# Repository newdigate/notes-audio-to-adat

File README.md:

# notes-audio-to-adat
* scrapbook for notes for audio-to-opto

# chipsets
## cool-audio
* http://coolaudio.com/docs/COOLAUDIO_V1401_DATASHEET.pdf
* http://coolaudio.com/docs/COOLAUDIO_V1402_DATASHEET.pdf

## wavefront 
* AL1401A
 * [datasheet](http://pdf.datasheetcatalog.com/datasheets2/15/156040_1.pdf)

# ADC
* Cirrus Logic 
  * CS5368-CQZ [datasheet](http://datasheet.octopart.com/CS5368-CQZ-Cirrus-Logic-datasheet-13402503.pdf)

# optical connectors
* TORX147 optical receiver
* PLR135/T10
  * PLR135 Series 2.4 to 5.5 V 16 Mbps 650 nm Photolink Fiber Optic Receiver
    * [snapEDA](https://www.snapeda.com/parts/PLR135/T10/Everlight%20Electronics%20Co%20Ltd/view-part/?ref=search&t=PLR135)
* Toshiba TOTX173
  * [octopart](https://octopart.com/totx173-toshiba-2173863?r=sp&s=UF4sqbTzTXCrdWtcyLfNBw)
  
# logic level converters
* AL1401A uses 5V logic, 3v3 to 5v required
* Texas Instruments 
  * CD40109BNSRG4 [datasheet](https://octopart.com/click/track?ct=datasheets&hlid=24875070&ppid=7109542&sid=370&sig=0583e53)
* The output signal of the AL1401 (i.e. to the fibre-optic LED) is ~0.9V, which needs to be converted to  between 2.5V and 5V5.

# micro-controllers
* xmos
  * XE216-512-TQ128-C20 (	digikey £12.43)

# reference designs
* https://www.xmos.com/download/xCORE-200-Multichannel-Audio-Platform-2V0-Hardware-Manual(1.4).pdf/

# misc links
https://jirin.web.althan.cz/201404-adater-the-lightpipe-interface-for-delta1010-rack/#

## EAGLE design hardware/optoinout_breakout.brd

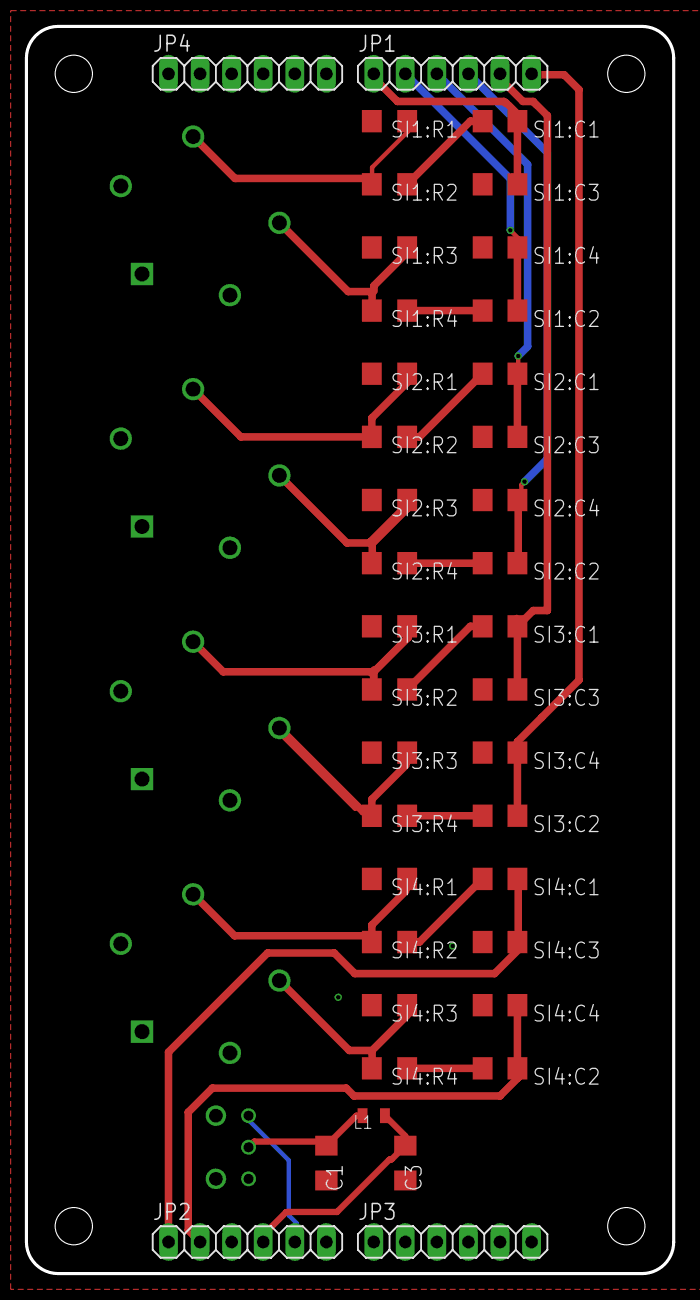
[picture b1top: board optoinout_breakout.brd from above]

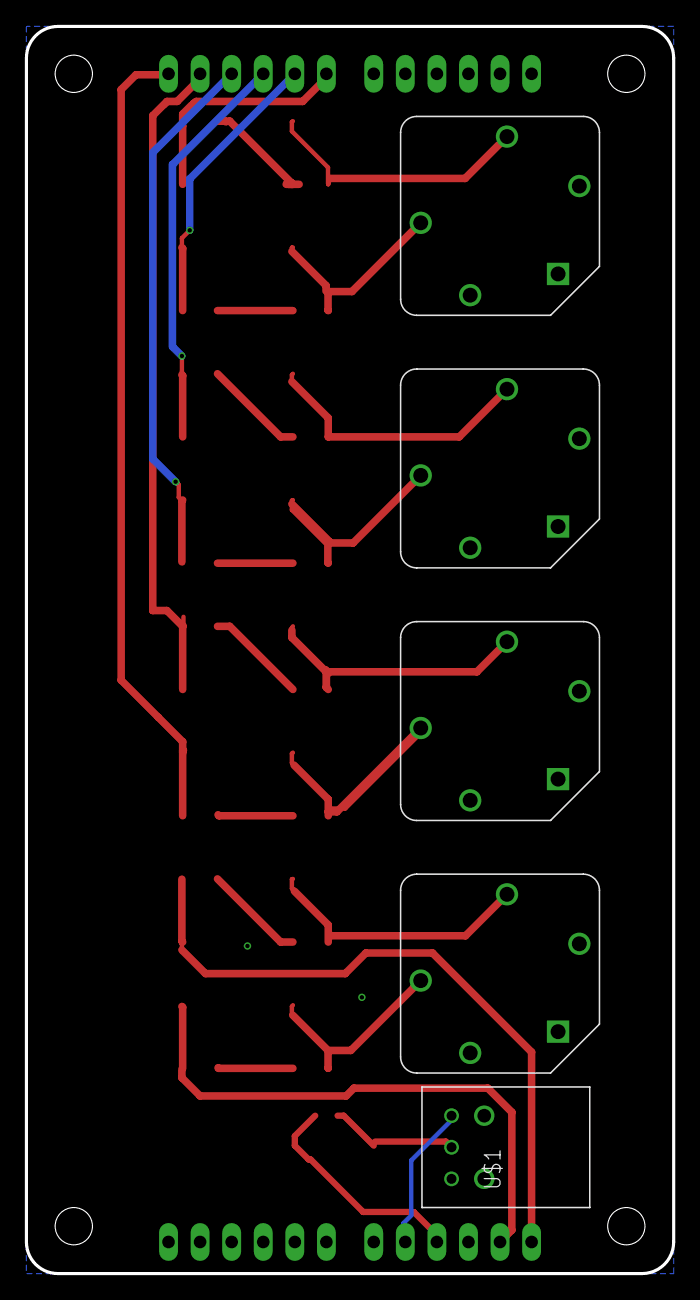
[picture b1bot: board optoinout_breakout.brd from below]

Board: 2 copper layers, 52.1 x 100.3 mm, 44 parts (5 on the bottom side), 28 nets.

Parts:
C1, C3: 100nF; C1206
JP1, JP2, JP3, JP4: 1X06
L1: 470R 500mA; L0805
SI1:C1, SI1:C2, SI2:C1, SI2:C2, SI3:C1, SI3:C2, SI4:C1, SI4:C2: 10uF; C1206
SI1:C3, SI1:C4, SI2:C3, SI2:C4, SI3:C3, SI3:C4, SI4:C3, SI4:C4: 2700pF; C1206
SI1:R1, SI1:R3, SI2:R1, SI2:R3, SI3:R1, SI3:R3, SI4:R1, SI4:R3: 100K; R1206
SI1:R2, SI1:R4, SI2:R2, SI2:R4, SI3:R2, SI3:R4, SI4:R2, SI4:R4: 150; R1206
SI1:U$3, SI2:U$3, SI3:U$3, SI4:U$3: ACJS-MV-5; ACJS-MV5
U$1: PLT133-T10W; PLR135-T10_PLT133-T10W

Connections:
3V3: C3.1, JP2.4, L1.P$1
AIN1+: JP1.1, SI1:C1.1, SI1:C3.1
AIN2+: JP1.2, SI1:C2.1, SI1:C4.1
AIN3+: JP1.3, SI2:C1.1, SI2:C3.1
AIN4+: JP1.4, SI2:C2.1, SI2:C4.1
AIN5+: JP1.5, SI3:C1.1, SI3:C3.1
AIN6+: JP1.6, SI3:C2.1, SI3:C4.1
AIN7+: JP2.1, SI4:C1.1, SI4:C3.1
AIN8+: JP2.2, SI4:C2.1, SI4:C4.1
GND: C1.2, C3.2, JP2.3, SI1:C3.2, SI1:C4.2, SI1:R1.1, SI1:R3.1, SI1:U$3.P$1, SI1:U$3.P$2, SI1:U$3.P$5, SI2:C3.2, SI2:C4.2, SI2:R1.1, SI2:R3.1, SI2:U$3.P$1, SI2:U$3.P$2, SI2:U$3.P$5, SI3:C3.2, SI3:C4.2, SI3:R1.1, SI3:R3.1, SI3:U$3.P$1, SI3:U$3.P$2, SI3:U$3.P$5, SI4:C3.2, SI4:C4.2, SI4:R1.1, SI4:R3.1, SI4:U$3.P$1, SI4:U$3.P$2, SI4:U$3.P$5, U$1.1
unnamed: C1.1, L1.P$2, U$1.2
OPOUT: JP2.5, U$1.3
SI1:N$1: SI1:R1.2, SI1:R2.1, SI1:U$3.P$4
SI1:N$7: SI1:C1.2, SI1:R2.2
SI1:N$10: SI1:R3.2, SI1:R4.1, SI1:U$3.P$3
SI1:N$11: SI1:C2.2, SI1:R4.2
SI2:N$1: SI2:R1.2, SI2:R2.1, SI2:U$3.P$4
SI2:N$7: SI2:C1.2, SI2:R2.2
SI2:N$10: SI2:R3.2, SI2:R4.1, SI2:U$3.P$3
SI2:N$11: SI2:C2.2, SI2:R4.2
SI3:N$1: SI3:R1.2, SI3:R2.1, SI3:U$3.P$4
SI3:N$7: SI3:C1.2, SI3:R2.2
SI3:N$10: SI3:R3.2, SI3:R4.1, SI3:U$3.P$3
SI3:N$11: SI3:C2.2, SI3:R4.2
SI4:N$1: SI4:R1.2, SI4:R2.1, SI4:U$3.P$4
SI4:N$7: SI4:C1.2, SI4:R2.2
SI4:N$10: SI4:R3.2, SI4:R4.1, SI4:U$3.P$3
SI4:N$11: SI4:C2.2, SI4:R4.2

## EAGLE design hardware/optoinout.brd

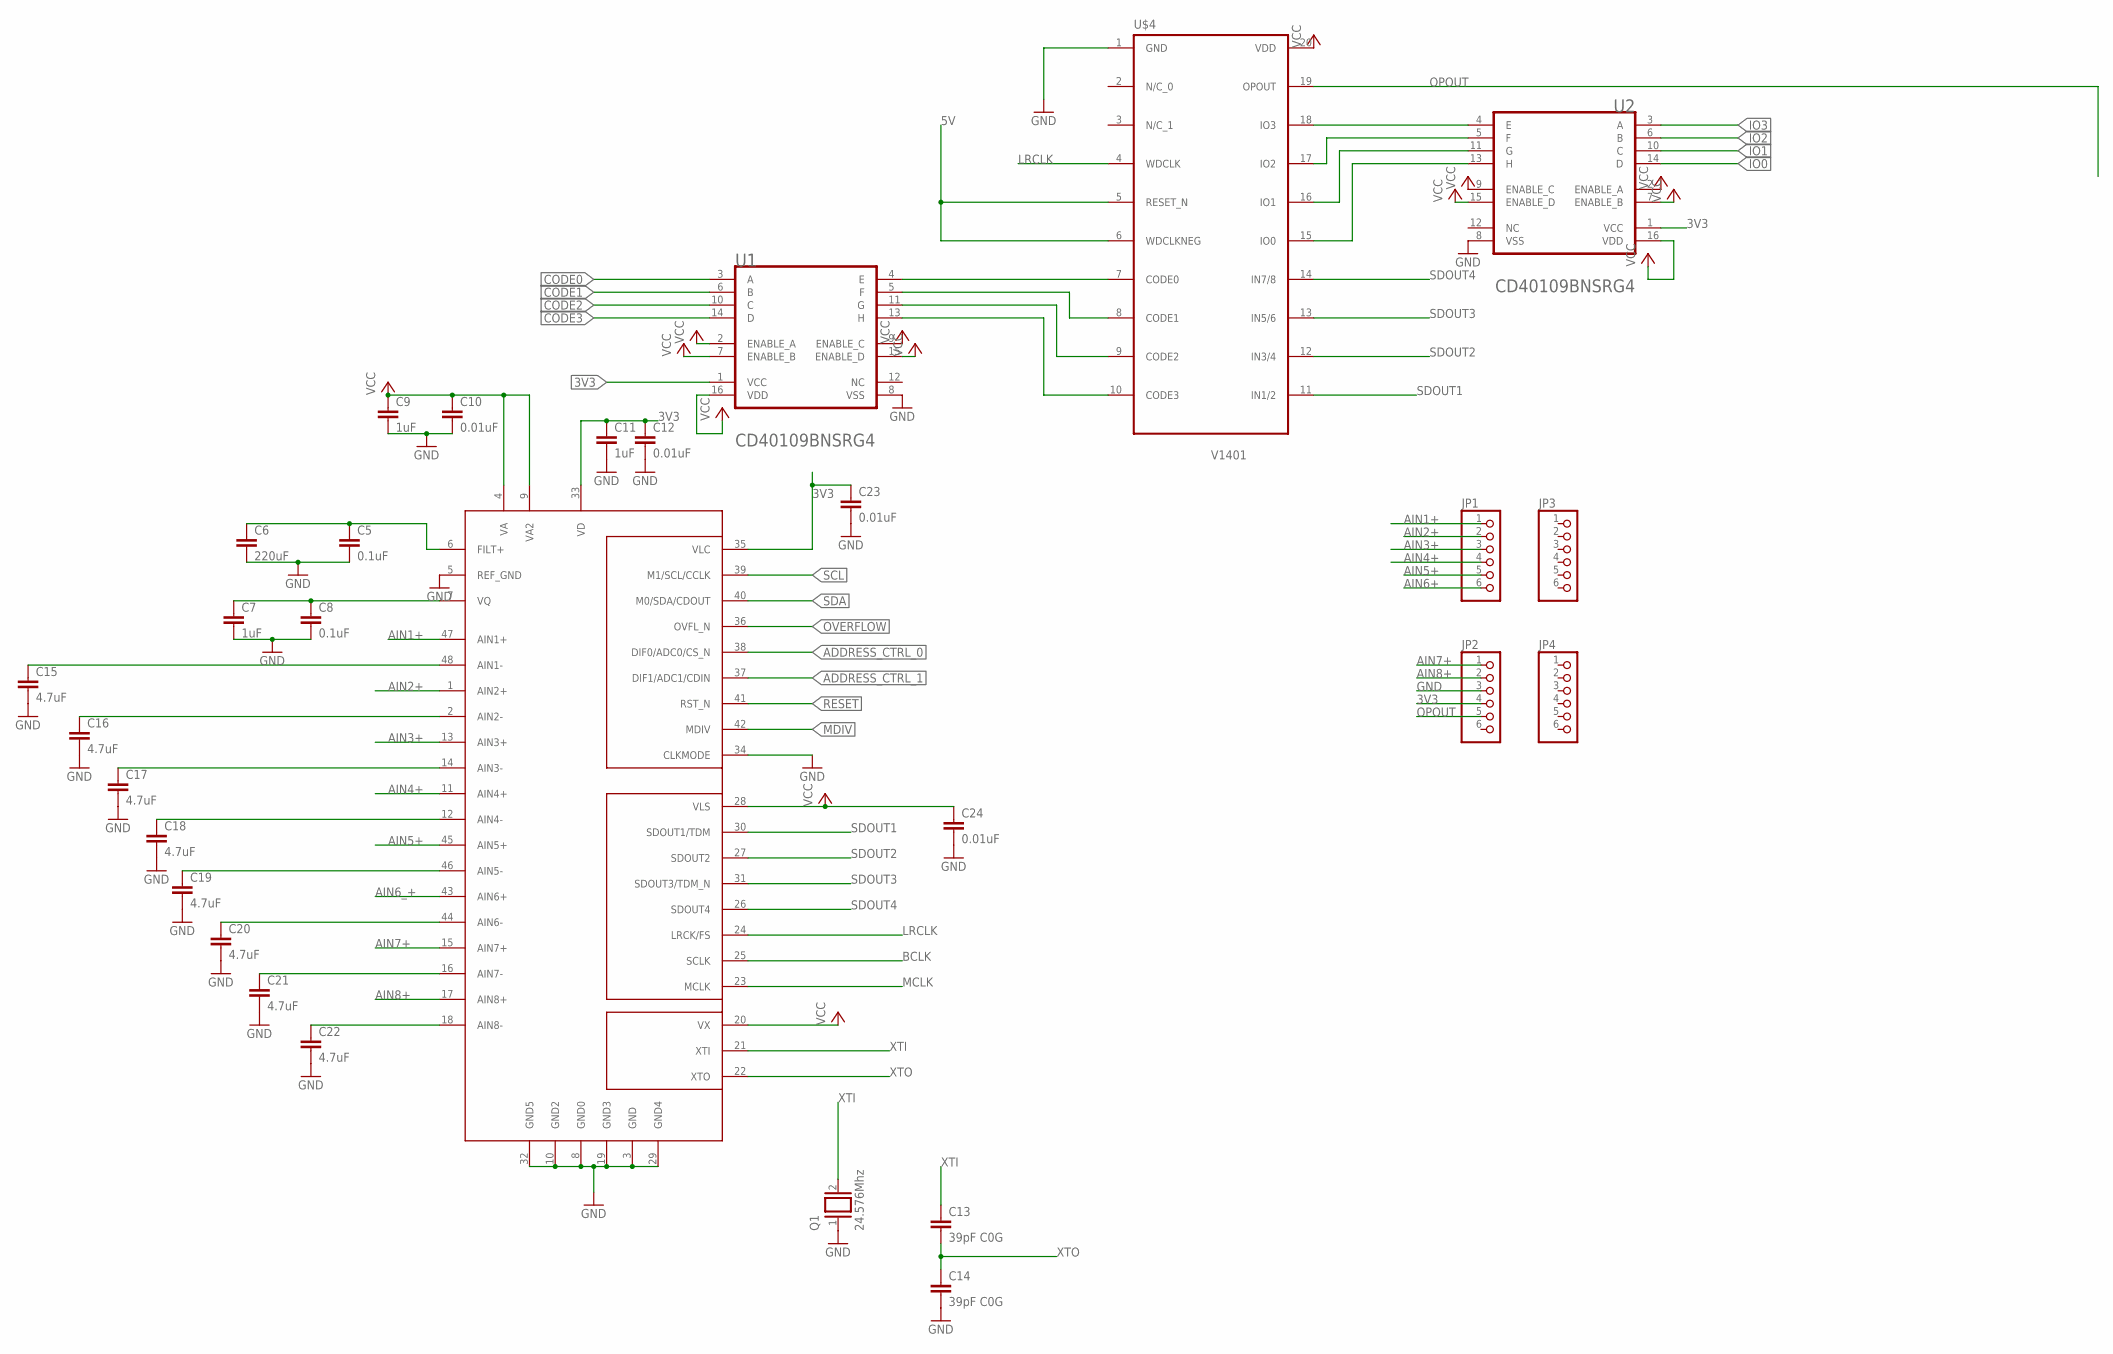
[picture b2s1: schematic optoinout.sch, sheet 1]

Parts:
C5, C8: 0.1uF; C1206
C6: 220uF; C1206
C7, C9, C11: 1uF; C1206
C10, C12, C23, C24: 0.01uF; C1206
C13, C14: 39pF C0G; C1206
C15, C16, C17, C18, C19, C20, C21, C22: 4.7uF; C1206
JP1, JP2, JP3, JP4: PINHD-1X6; 1X06
Q1: 24.576Mhz; QS
U1, U2: TEXAS_INSTRUMENTS_CD40109BNSRG4TEXAS_INSTRUMENTS_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; TEXAS_INSTRUMENTS_CD40109BNSRG4_0
U$3: CS5368-2; QFP50P900X900X160-48N
U$4: V1401; SOP20

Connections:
3V3: C11.1, C12.1, C23.1, JP2.4, U1.1 (VCC), U2.1 (VCC), U$3.33 (VD), U$3.35 (VLC); also elsewhere on the board
5V: U$4.5 (RESET_N), U$4.6 (WDCLKNEG)
ADDRESS_CTRL_0: U$3.38 (DIF0/ADC0/CS_N); also elsewhere on the board
ADDRESS_CTRL_1: U$3.37 (DIF1/ADC1/CDIN); also elsewhere on the board
AIN1+: JP1.1, U$3.47 (AIN1+)
AIN2+: JP1.2, U$3.1 (AIN2+)
AIN3+: JP1.3, U$3.13 (AIN3+)
AIN4+: JP1.4, U$3.11 (AIN4+)
AIN5+: JP1.5, U$3.45 (AIN5+)
AIN6+: JP1.6
AIN6_+: U$3.43 (AIN6+)
AIN7+: JP2.1, U$3.15 (AIN7+)
AIN8+: JP2.2, U$3.17 (AIN8+)
BCLK: U$3.25 (SCLK)
CODE0: U1.3 (A); also elsewhere on the board
CODE1: U1.6 (B); also elsewhere on the board
CODE2: U1.10 (C); also elsewhere on the board
CODE3: U1.14 (D); also elsewhere on the board
GND: C5.2, C6.2, C7.2, C8.2, C9.2, C10.2, C11.2, C12.2, C14.2, C15.2, C16.2, C17.2, C18.2, C19.2, C20.2, C21.2, C22.2, C23.2, C24.2, JP2.3, Q1.1, U1.8 (VSS), U2.8 (VSS), U$3.3 (GND), U$3.5 (REF_GND), U$3.8 (GND0), U$3.10 (GND2), U$3.19 (GND3), U$3.29 (GND4), U$3.32 (GND5), U$3.34 (CLKMODE), U$4.1 (GND); also elsewhere on the board
IO0: U2.14 (D); also elsewhere on the board
IO1: U2.10 (C); also elsewhere on the board
IO2: U2.6 (B); also elsewhere on the board
IO3: U2.3 (A); also elsewhere on the board
LRCLK: U$3.24 (LRCK/FS), U$4.4 (WDCLK)
MCLK: U$3.23 (MCLK)
MDIV: U$3.42 (MDIV); also elsewhere on the board
unnamed: C7.1, C8.1, U$3.7 (VQ)
unnamed: U1.4 (E), U$4.7 (CODE0)
unnamed: C5.1, C6.1, U$3.6 (FILT+)
unnamed: U1.5 (F), U$4.8 (CODE1)
unnamed: U1.11 (G), U$4.9 (CODE2)
unnamed: U1.13 (H), U$4.10 (CODE3)
unnamed: C16.1, U$3.2 (AIN2-)
unnamed: C15.1, U$3.48 (AIN1-)
unnamed: C17.1, U$3.14 (AIN3-)
unnamed: C18.1, U$3.12 (AIN4-)
unnamed: C19.1, U$3.46 (AIN5-)
unnamed: C20.1, U$3.44 (AIN6-)
unnamed: C21.1, U$3.16 (AIN7-)
unnamed: C22.1, U$3.18 (AIN8-)
unnamed: U2.4 (E), U$4.18 (IO3)
unnamed: U2.5 (F), U$4.17 (IO2)
unnamed: U2.11 (G), U$4.16 (IO1)
unnamed: U2.13 (H), U$4.15 (IO0)
OPOUT: JP2.5, U$4.19 (OPOUT)
OVERFLOW: U$3.36 (OVFL_N); also elsewhere on the board
RESET: U$3.41 (RST_N); also elsewhere on the board
SCL: U$3.39 (M1/SCL/CCLK); also elsewhere on the board
SDA: U$3.40 (M0/SDA/CDOUT); also elsewhere on the board
SDOUT1: U$3.30 (SDOUT1/TDM), U$4.11 (IN1/2)
SDOUT2: U$3.27 (SDOUT2), U$4.12 (IN3/4)
SDOUT3: U$3.31 (SDOUT3/TDM_N), U$4.13 (IN5/6)
SDOUT4: U$3.26 (SDOUT4), U$4.14 (IN7/8)
VCC: C9.1, C10.1, C24.1, U1.2 (ENABLE_A), U1.7 (ENABLE_B), U1.9 (ENABLE_C), U1.15 (ENABLE_D), U1.16 (VDD), U2.2 (ENABLE_A), U2.7 (ENABLE_B), U2.9 (ENABLE_C), U2.15 (ENABLE_D), U2.16 (VDD), U$3.4 (VA), U$3.9 (VA2), U$3.20 (VX), U$3.28 (VLS), U$4.20 (VDD); also elsewhere on the board
XTI: C13.1, Q1.2, U$3.21 (XTI)
XTO: C13.2, C14.1, U$3.22 (XTO)

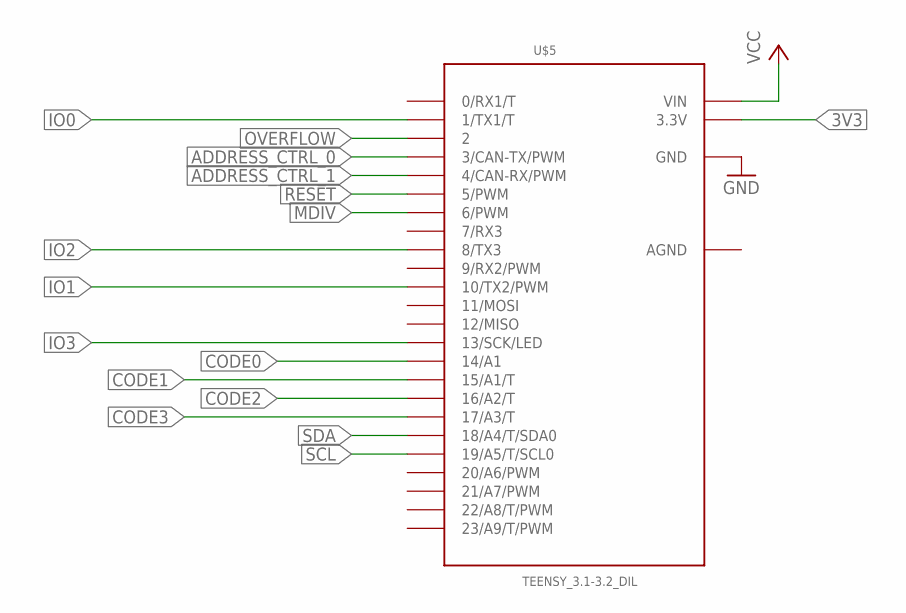
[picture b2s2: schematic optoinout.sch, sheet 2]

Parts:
U$5: TEENSY_3.1-3.2_DIL; TEENSY_3.0-3.2&LC_DIL

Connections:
3V3: U$5.3.3V; also elsewhere on the board
ADDRESS_CTRL_0: U$5.3 (3/CAN-TX/PWM); also elsewhere on the board
ADDRESS_CTRL_1: U$5.4 (4/CAN-RX/PWM); also elsewhere on the board
AGND: U$5.AGND
CODE0: U$5.14/A0 (14/A1); also elsewhere on the board
CODE1: U$5.15/A1 (15/A1/T); also elsewhere on the board
CODE2: U$5.16/A2 (16/A2/T); also elsewhere on the board
CODE3: U$5.17/A3 (17/A3/T); also elsewhere on the board
GND: U$5.GND; also elsewhere on the board
IO0: U$5.1 (1/TX1/T); also elsewhere on the board
IO1: U$5.10 (10/TX2/PWM); also elsewhere on the board
IO2: U$5.8 (8/TX3); also elsewhere on the board
IO3: U$5.13 (13/SCK/LED); also elsewhere on the board
MDIV: U$5.6 (6/PWM); also elsewhere on the board
OVERFLOW: U$5.2; also elsewhere on the board
RESET: U$5.5 (5/PWM); also elsewhere on the board
SCL: U$5.19/A5 (19/A5/T/SCL0); also elsewhere on the board
SDA: U$5.18/A4 (18/A4/T/SDA0); also elsewhere on the board
VCC: U$5.VIN; also elsewhere on the board

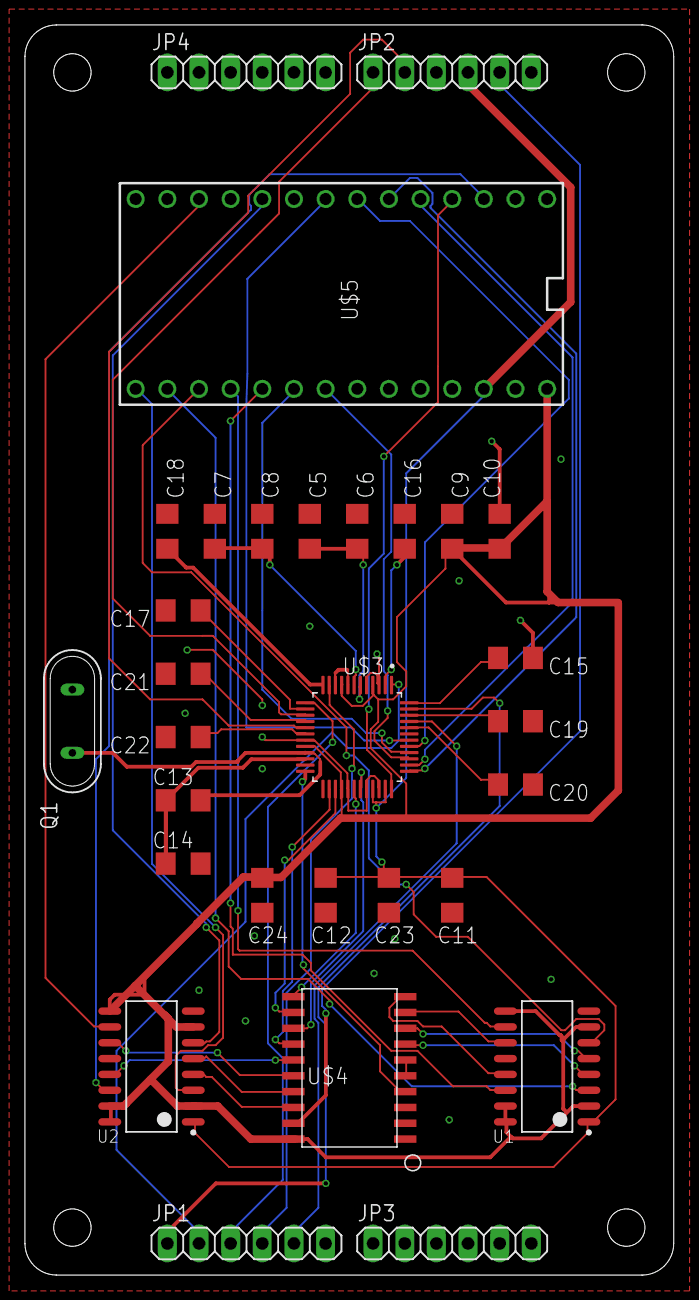
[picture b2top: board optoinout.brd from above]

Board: 2 copper layers, 52.1 x 100.3 mm, 30 parts (0 on the bottom side), 52 nets.

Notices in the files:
parts and their libraries:
coolaudio: Copyright (C) 2010, Bob Starr
